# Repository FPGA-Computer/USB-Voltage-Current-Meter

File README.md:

USB Meter
=========

This is the repository for my KW203 USB meter mod.
This mod is provided as is. This is a mod, so no full schematics.

The KW203 USB meter like most of those in the price range have very lousy
resolution and cannot read low currents.  This mod is replacing the
unknown microcontroller with a STM8S003F3 and a few modification to 
improve on the resolution and accuracy. The modifications and the 
calibration is what makes this a usable test equipment.

This is a hack that depends on the existing questionable components i.e. 
3V LDO (+/-3%) and current sensing resistor (??? %). 

Each unit has to be calibrated against a multimeter with a linear 
regression for reasonable accuracy. The current measurement suffers
from non-linearity at high current due to heating effects on the sense 
resistor and the bad layout traces. Trimppot won't help here.  To manage 
the errors, I use a piecewise linear fit. 

Firmware is written for Cosmic C which ST arranged to have for free use 
with their STM8 chips.

Project page: mod, documentations, photos

https://hw-by-design.blogspot.com/2019/08/usb-meter-modding.html

https://hw-by-design.blogspot.com/2019/09/usb-meter-modding-part-2.html

https://hw-by-design.blogspot.com/2019/10/uc-mod-pcb-part-3.html

Licensing:

Schematic/PCB: Creative Commons 4.0 Attribution-ShareAlike 4.0 International

Firmware: source code: GPL v3

Updates:

New PCB for the adapter board - verified.

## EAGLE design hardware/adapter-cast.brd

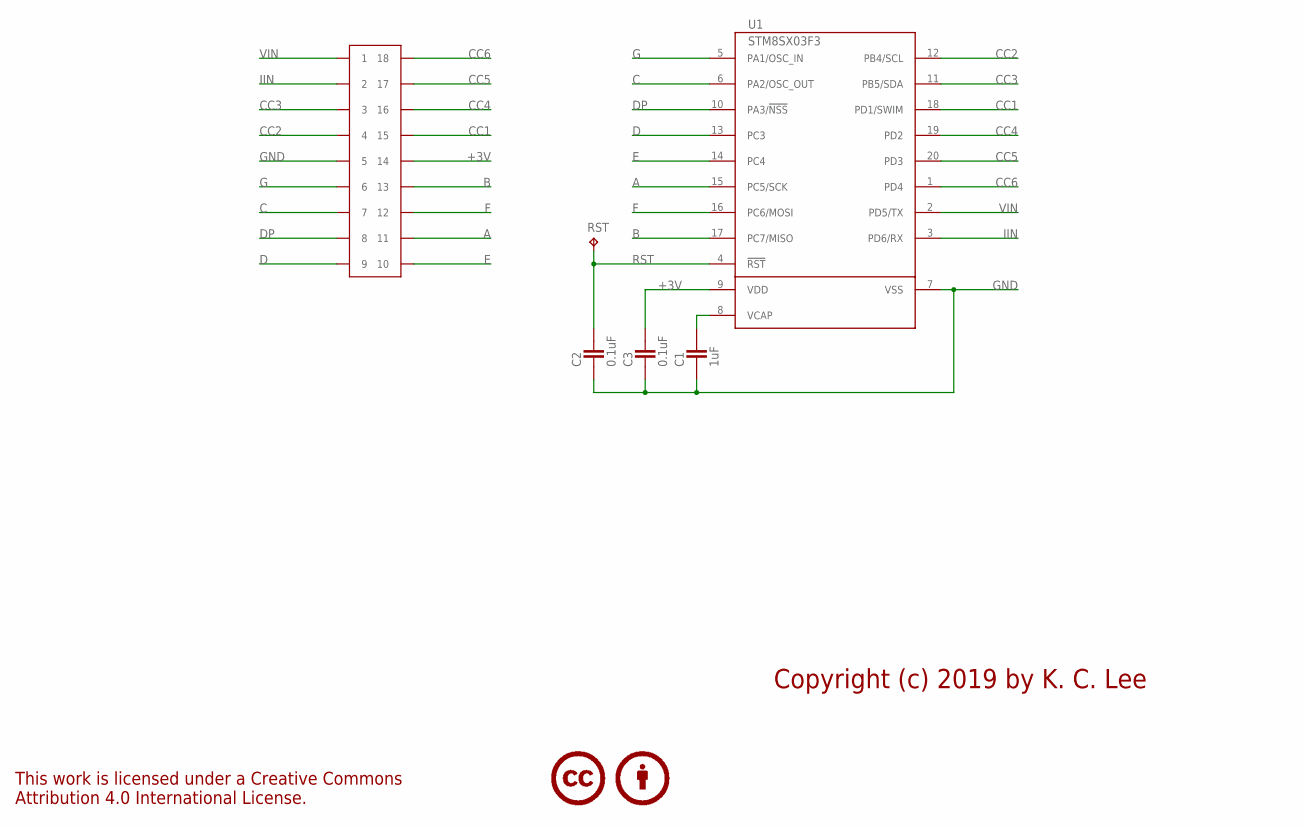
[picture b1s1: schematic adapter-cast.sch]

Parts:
C1: 1uF; CAPC1608X92N
C2, C3: 0.1uF; CAPC1608X92N
LICENSE1: CC-BYNONE; CC-NONE
P1: DUMMY-SO18WCAST; SO18W-CAST
RST: TP; TP11SQ
U1: STM8SX03F3; TSSOP20

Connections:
+3V: C3.2, P1.P$14 (14), U1.9 (VDD)
A: P1.P$11 (11), U1.15 (PC5/SCK)
B: P1.P$13 (13), U1.17 (PC7/MISO)
C: P1.P$7 (7), U1.6 (PA2/OSC_OUT)
CC1: P1.P$15 (15), U1.18 (PD1/SWIM)
CC2: P1.P$4 (4), U1.12 (PB4/SCL)
CC3: P1.P$3 (3), U1.11 (PB5/SDA)
CC4: P1.P$16 (16), U1.19 (PD2)
CC5: P1.P$17 (17), U1.20 (PD3)
CC6: P1.P$18 (18), U1.1 (PD4)
D: P1.P$9 (9), U1.13 (PC3)
DP: P1.P$8 (8), U1.10 (PA3/!NSS)
E: P1.P$10 (10), U1.14 (PC4)
F: P1.P$12 (12), U1.16 (PC6/MOSI)
G: P1.P$6 (6), U1.5 (PA1/OSC_IN)
GND: C1.1, C2.1, C3.1, P1.P$5 (5), U1.7 (VSS)
IIN: P1.P$2 (2), U1.3 (PD6/RX)
unnamed: C1.2, U1.8 (VCAP)
RST: C2.2, RST.TP, U1.4 (!RST)
VIN: P1.P$1 (1), U1.2 (PD5/TX)

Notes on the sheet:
Copyright (c) 2019 by K. C. Lee

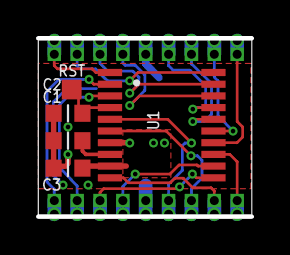
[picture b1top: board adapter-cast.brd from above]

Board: 2 copper layers, 11.9 x 9.9 mm, 7 parts (0 on the bottom side), 20 nets.

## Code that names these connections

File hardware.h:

/*
 * hardware.h
 *
 * Created: August 30, 2019, 6:07:55 PM
 *  Author: K. C. Lee
 * Copyright (c) 2016 by K. C. Lee
 
 This program is free software: you can redistribute it and/or modify
 it under the terms of the GNU General Public License as published by
 the Free Software Foundation, either version 3 of the License, or
 (at your option) any later version.

 This program is distributed in the hope that it will be useful,
 but WITHOUT ANY WARRANTY; without even the implied warranty of
 MERCHANTABILITY or FITNESS FOR A PARTICULAR PURPOSE.  See the
 GNU General Public License for more details.

 You should have received a copy of the GNU General Public License
 along with this program.

 If not, see http://www.gnu.org/licenses/gpl-3.0.en.html 
 */ 

#ifndef HARDWARE_H_
#define HARDWARE_H_

#ifndef __CSMC__
#define __CSMC__
#endif
#define STM8S003

#include "stm8s.h"
#include <stdio.h>

// STM8S003F3P6
enum _PA { PA1=0x02, PA2=0x04, PA3=0x08 };
enum _PB { PB4=0x10, PB5=0x20 };
enum _PC { PC3=0x08, PC4=0x10, PC5=0x20, PC6=0x40, PC7=0x80 };
enum _PD { PD1=0x02, PD2=0x04, PD3=0x08, PD4=0x10, PD5=0x20, PD6=0x40 };

enum _IO7SEG
{ 
	IOSEG_G=PA1,IOSEG_C=PA2,IOSEG_DP=PA3,
	IOSEG_D=PC3,IOSEG_E=PC4,IOSEG_A=PC5,IOSEG_F=PC6,IOSEG_B=PC7
};

enum _7SEG_ENCODE
{
	SEG_G=IOSEG_G>>1,SEG_C=IOSEG_C>>1,SEG_DP=IOSEG_DP>>1,
	SEG_D=IOSEG_D,SEG_E=IOSEG_E,SEG_A=IOSEG_A,SEG_F=IOSEG_F,SEG_B=IOSEG_B
};

enum _CC_DRV
{ 
	CC2=PB4,CC2_PORT=GPIOB_BaseAddress,
	CC3=PB5,CC3_PORT=GPIOB_BaseAddress,
	CC1=PD1,CC1_PORT=GPIOD_BaseAddress,
	CC4=PD2,CC4_PORT=GPIOD_BaseAddress,
	CC5=PD3,CC5_PORT=GPIOD_BaseAddress,
	CC6=PD4,CC6_PORT=GPIOD_BaseAddress
};


#define PA_SEGS	(IOSEG_C|IOSEG_G|IOSEG_DP)
#define PB_COLS	(CC2|CC3)
#define PC_SEGS	(IOSEG_D|IOSEG_E|IOSEG_A|IOSEG_F|IOSEG_B)
#define PD_COLS	(CC1|CC4|CC5|CC6)

#define PORTA_SEG(X)		(((X) & (PA_SEGS>>1))<<1)
#define PORTC_SEG(X)		((X) & PC_SEGS)

#define GPIO_ODR(X)			((GPIO_TypeDef *)(X))->ODR

#define COLUMN_MAX			6

#define VOLTAGE_COL			0
#define CURRENT_COL			3

typedef struct 
{
	uint8_t		Bit;
	uint16_t	Port;
} Column_Drv_t;

#include "irq.h"

#define CPU_CLK					2000000UL

// 16MHz/4096 -> 3906Hz
#define TIM2_PSCR				0x0c
// reload for 355Hz/6 columns -> 59Hz
#define TIM2_ARRH				0x00
#define TIM2_ARRL				0x0a
// update every 12 display refresh
#define TICK_MAX				(COLUMN_MAX*12-1)

// ADC clock div = 1/8
#define ADC_CLKDIV			0x20

#define ADC_OVERSAMPLE	16
#define ADC_DECIMATE		4

#define ADC_AVERAGES		4

#define VIN_CH					5
#define IIN_CH					6

#define CHAR_O					(SEG_A|SEG_B|SEG_C|SEG_D|SEG_E|SEG_F)
#define CHAR_L					(SEG_D|SEG_E|SEG_F)
#define CHAR_V					(SEG_B|SEG_C|SEG_D|SEG_E|SEG_F)

#define ZERO_SUP				0x80
#define COL_MASK				0x0f

#define VIN_LOW					319
#define VIN_HIGH				1019
#define V_RANGE					1000
#define I_RANGE					1000

extern volatile uint8_t tick,update;
extern volatile uint8_t Display[];
extern const uint8_t CharMap[];

void Init_Hardware(void);
void Update(void);
uint16_t ADC_Conv(uint8_t Ch);

#endif

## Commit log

2019-09-13 added PCB
2019-09-13 cleanup
2019-10-05 mod update

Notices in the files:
parts and their libraries:
Misc logo: This work is licensed under a Creative Commons
Attribution 4.0 International License.
